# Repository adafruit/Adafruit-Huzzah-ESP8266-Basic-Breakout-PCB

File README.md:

# Adafruit Huzzah ESP8266 Basic Breakout PCB
<a href="http://www.adafruit.com/products/2471"><br/>
Click here to purchase one from the Adafruit shop</a>

Add Internet to your next project with an adorable, bite-sized WiFi microcontroller, at a price you like! The ESP8266 processor from Espressif is an 80 MHz microcontroller with a full WiFi front-end (both as client and access point) and TCP/IP stack with DNS support as well. While this chip has been very popular, its also been very difficult to use. Most of the low cost modules are not breadboard friendly, don't have an onboard 500mA 3.3V regulator or level shifting, and aren't CE or FCC emitter certified....UNTIL NOW!

The Adafruit HUZZAH ESP8266 breakout is what we designed to make working with this chip super easy and a lot of fun. We took a certified module with an onboard antenna, and plenty of pins, and soldered it onto our designed breakout PCBs.

PCB files for Adafruit Huzzah ESP8266 Basic Breakout, The format is EagleCAD schematic and board layout

For more details, check out the product page at http://www.adafruit.com/products/2471

### License

Adafruit invests time and resources providing this open source design, please support Adafruit and open-source hardware by purchasing products from [Adafruit](https://www.adafruit.com)!

All text above must be included in any redistribution

Designed by Limor Fried/Ladyada for Adafruit Industries.
Creative Commons Attribution/Share-Alike, all text above must be included in any redistribution. 
See license.txt for additional information.

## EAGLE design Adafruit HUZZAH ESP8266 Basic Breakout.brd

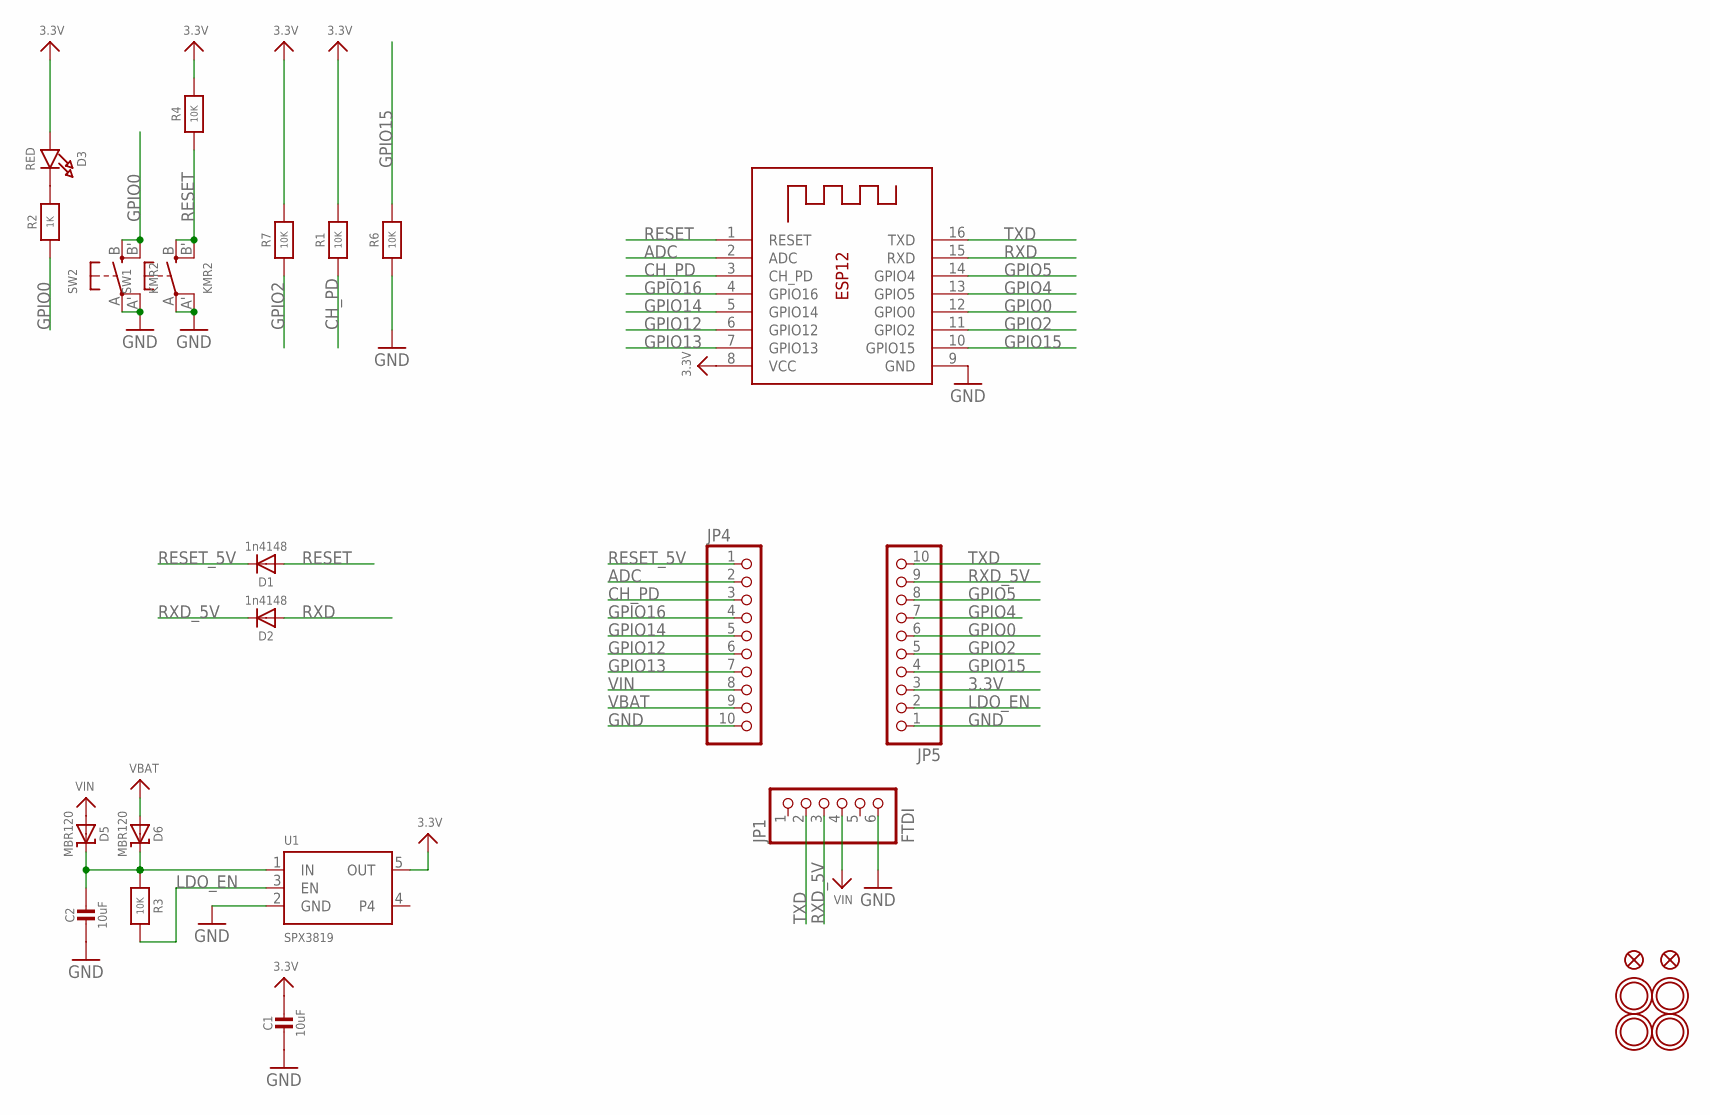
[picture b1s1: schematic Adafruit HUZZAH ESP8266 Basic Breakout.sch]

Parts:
C1, C2: 10uF; 0805-NO
D1, D2: 1n4148; SOD-323
D3: RED; CHIPLED_0805_NOOUTLINE
D5, D6: MBR120; SOD-123
FID1, FID3: FIDUCIAL""; FIDUCIAL_1MM
JP1: FTDI; 1X06_ROUND_70
JP4, JP5: HEADER-1X1070MIL; 1X10_ROUND70
R1, R3, R4, R6, R7: 10K; 0805-NO
R2: 1K; 0805-NO
SW1, SW2: KMR2; BTN_KMR2_4.6X2.8
U1: SPX3819; SOT23-5
U$15, U$16, U$17, U$18: MOUNTINGHOLE2.5; MOUNTINGHOLE_2.5_PLATED
X1: ESP-12

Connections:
3.3V: C1.1, D3.A, JP5.3, R1.2, R4.2, R7.2, U1.5 (OUT), X1.8 (VCC)
ADC: JP4.2, X1.2 (ADC)
CH_PD: JP4.3, R1.1, X1.3 (CH_PD)
GND: C1.2, C2.2, JP1.6, JP4.10, JP5.1, R6.1, SW1.A, SW1.A' (P1), SW2.A, SW2.A' (P1), U1.2 (GND), X1.9 (GND)
GPIO0: JP5.6, R2.1, SW2.B (S), SW2.B' (S1), X1.12 (GPIO0)
GPIO2: JP5.5, R7.1, X1.11 (GPIO2)
GPIO4: JP5.7, X1.13 (GPIO5)
GPIO5: JP5.8, X1.14 (GPIO4)
GPIO12: JP4.6, X1.6 (GPIO12)
GPIO13: JP4.7, X1.7 (GPIO13)
GPIO14: JP4.5, X1.5 (GPIO14)
GPIO15: JP5.4, R6.2, X1.10 (GPIO15)
GPIO16: JP4.4, X1.4 (GPIO16)
LDO_EN: JP5.2, R3.2, U1.3 (EN)
unnamed: D3.C, R2.2
unnamed: C2.1, D5.C, D6.C, R3.1, U1.1 (IN)
RESET: D1.A, R4.1, SW1.B (S), SW1.B' (S1), X1.1 (RESET)
RESET_5V: D1.C, JP4.1
RXD: D2.A, X1.15 (RXD)
RXD_5V: D2.C, JP1.3, JP5.9
TXD: JP1.2, JP5.10, X1.16 (TXD)
VBAT: D6.A, JP4.9
VIN: D5.A, JP1.4, JP4.8

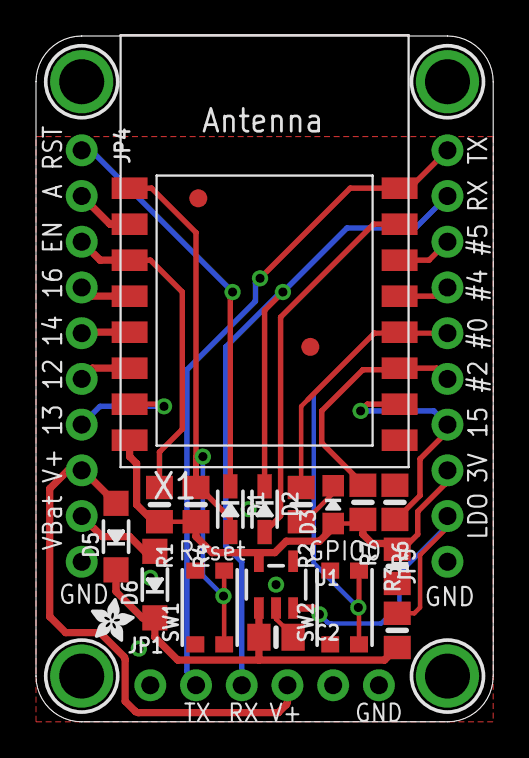
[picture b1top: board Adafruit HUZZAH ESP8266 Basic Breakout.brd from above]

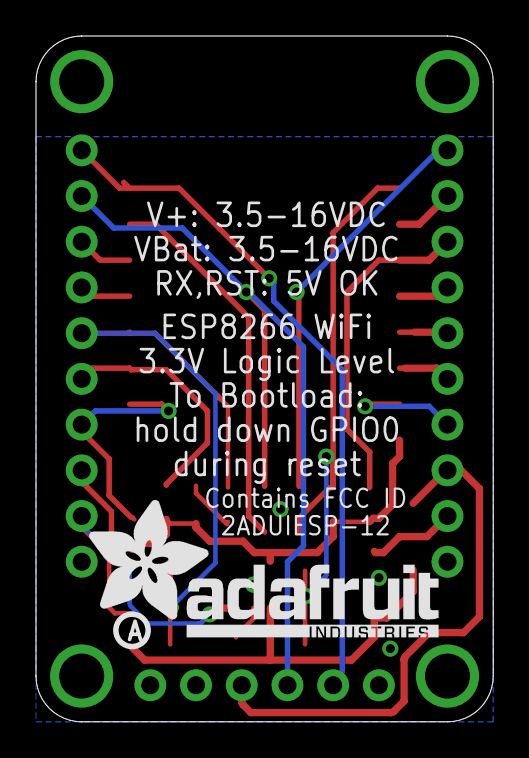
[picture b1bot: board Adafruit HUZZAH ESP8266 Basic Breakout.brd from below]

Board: 2 copper layers, 25.4 x 38.1 mm, 30 parts (3 on the bottom side), 23 nets.

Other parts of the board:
U$2: HUZZAHLOGO
U$3: ADAFRUIT_2.5MM
U$12: ADAFRUIT_TEXT_20MM
U$13: PCBFEAT-REV-040

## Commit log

2015-05-26 init

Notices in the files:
parts and their libraries:
microbuilder: This work is placed in the public domain, and may be freely used for commercial and non-commercial work with the following conditions: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
